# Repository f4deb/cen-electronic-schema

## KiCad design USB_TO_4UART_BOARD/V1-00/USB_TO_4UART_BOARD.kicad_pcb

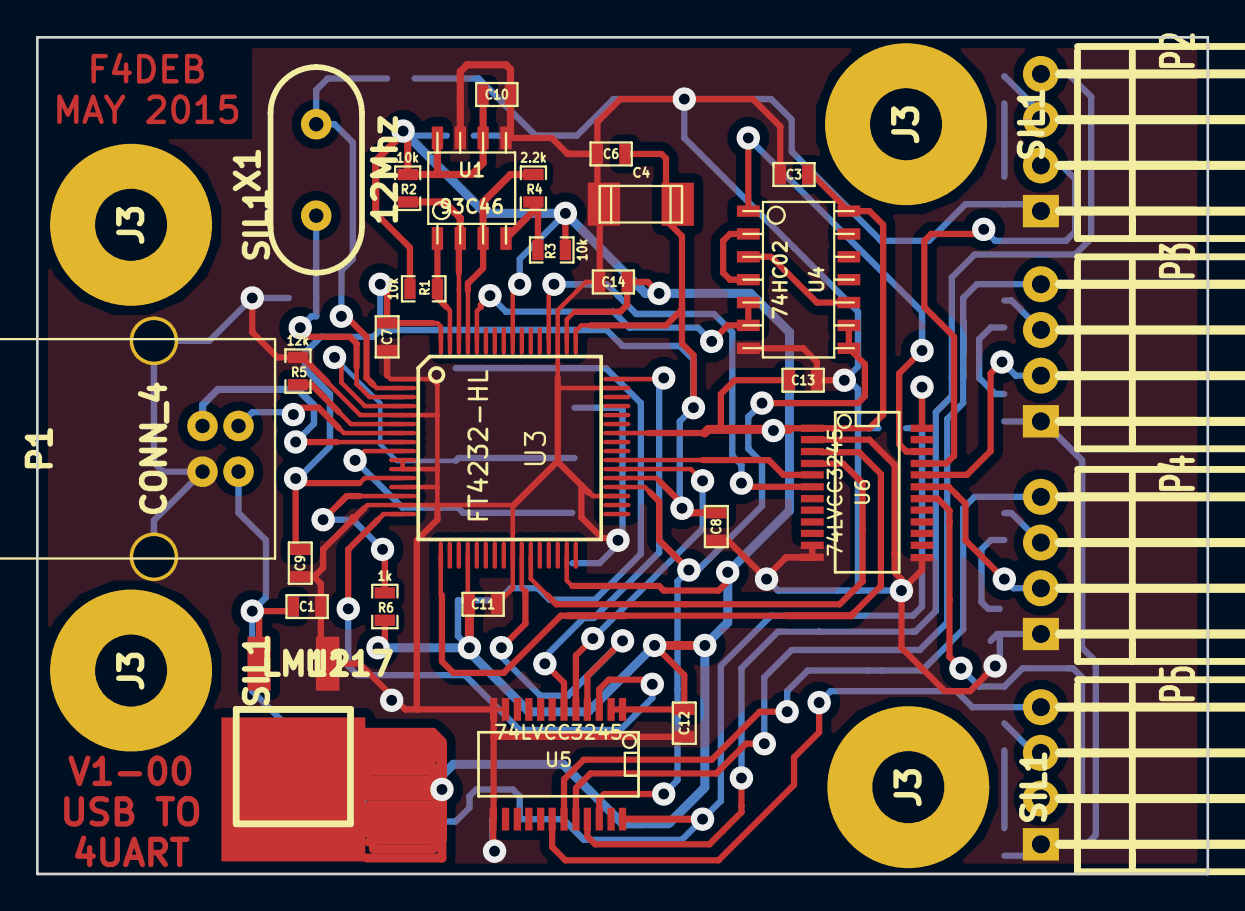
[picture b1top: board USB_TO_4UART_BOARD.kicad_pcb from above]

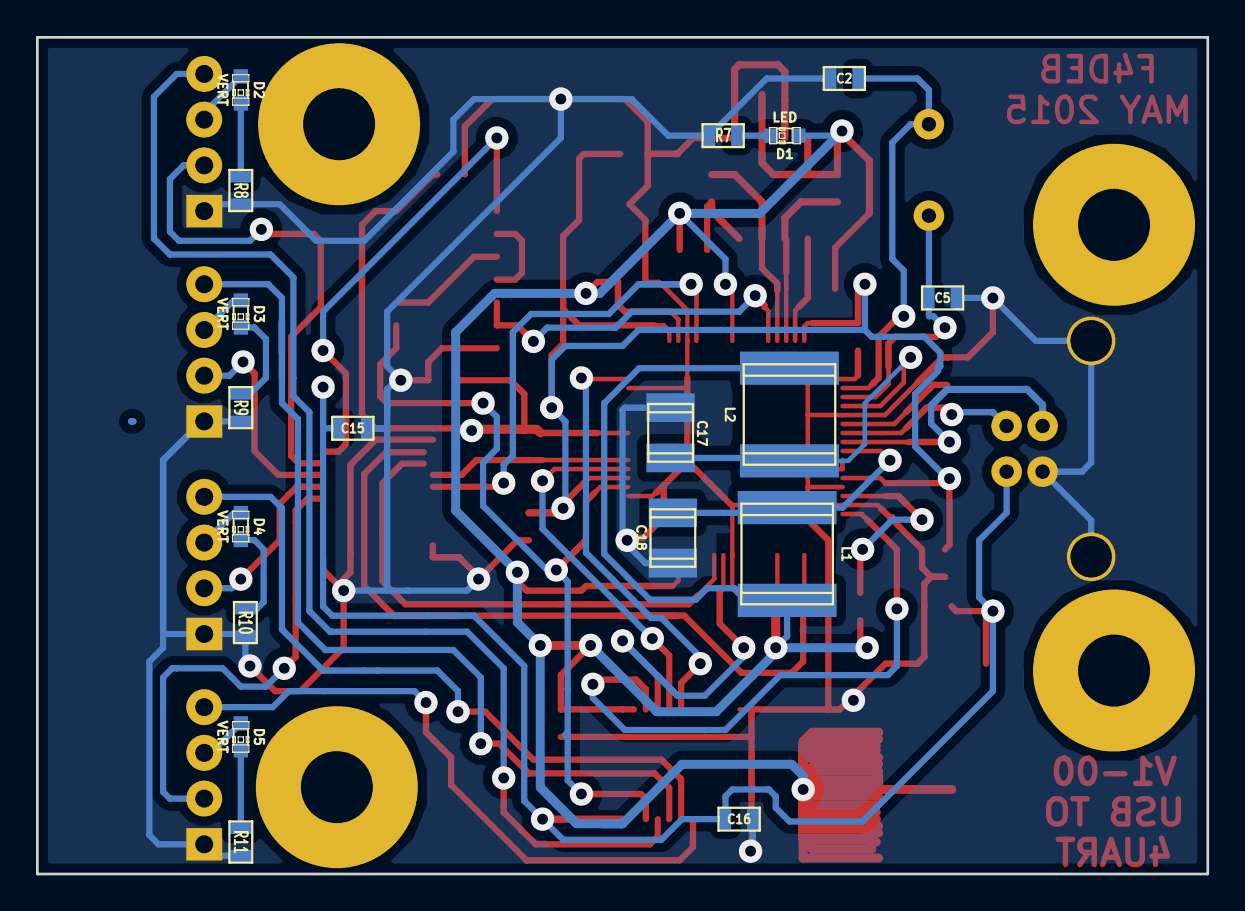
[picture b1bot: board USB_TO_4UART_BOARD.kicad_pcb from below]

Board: 2 copper layers, 65.0 x 46.5 mm, 52 parts (18 on the bottom side), 46 nets.

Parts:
C1, C3, C6, C7, C8, C9, C10, C11, C12, C13, C14, C15, C16: 100n; SM0603_Capa
C2, C5: 27p; SM0603_Capa
C4: 10uF/10V; c_1808
C17, C18: 10uF/10V; SM1210
D1: LED; LED-0603
D2, D3, D4, D5: VERT; LED-0603
J3, J3#2, J3#3, J3#4: SIL1; COLONETTE
L1, L2: 39uH; c_2220
P1: CONN_4; USB_B
P2, P3, P4, P5: CONN_4; SIL-3_1_2-4-HOR
R1, R2, R3: 10k; SM0603_Resistor
R4: 2.2k; SM0603_Resistor
R5: 12k; SM0603_Resistor
R6, R8, R9, R10, R11: 1k; SM0603_Resistor
R7: 470; SM0603_Resistor
U1: 93C46; so-8
U2: LM1117; DPAK
U3: FT4232-HL; TQFP_64
U4: 74HC02; so-14
U5, U6: 74LVCC3245; SSOP24
X1: 12Mhz; HC-49V

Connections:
+1.8V: C4.1, C6.1, C7.1, C8.1, C9.1, U3.12, U3.37, U3.49, U3.64
+3.3V: C3.1, C10.1, C11.1, C12.1, C13.1, C14.1, D1.1, L1.1, L2.1, R1.1, R2.1, R3.1, R6.2, U1.6, U1.8, U2.3, U3.20, U3.31, U3.42, U3.50, U3.56, U4.14, U5.1, U5.2, U6.1
+5VD: C1.1, C15.1, C16.1, P1.1, U2.2, U5.24, U6.24
/PWREN: U3.60, U4.5, U4.6
/RXD0: U3.17, U6.3
/RXD0_5V: P2.2, U6.21
/RXD1: U3.27, U6.4
/RXD1_5V: P3.2, U6.20
/RXD2: U3.39, U6.5
/RXD2_5V: P4.2, U6.19
/RXD3: U3.52, U6.6
/RXD3_5V: P5.2, U6.18
/SUSPEND: U3.36, U4.8, U4.9, U5.22
/TXD0: U3.16, U5.3
/TXD0_5V: P2.4, U5.21
/TXD1: U3.26, U5.4
/TXD1_5V: P3.4, U5.20
/TXD2: U3.38, U5.5
/TXD2_5V: P4.4, U5.19
/TXD3: U3.48, U5.6
/TXD3_5V: P5.4, U5.18
/UART0: D2.1, P2.3
/UART1: D3.1, P3.3
/UART2: D4.1, P4.3
/UART3: D5.1, P5.3
GND: C1.2, C2.1, C3.2, C4.2, C5.1, C6.2, C7.2, C8.2, C9.2, C10.2, C11.2, C12.2, C13.2, C14.2, C15.2, C16.2, C17.2, C18.2, P1.4, P1.5, P1.6, P2.1, P3.1, P4.1, P5.1, R5.1, R7.2, R8.2, R9.2, R10.2, R11.2, U1.5, U1.7, U2.1, U3.1, U3.5, U3.10, U3.11, U3.13, U3.15, U3.25, U3.35, U3.47, U3.51, U4.7, U5.11, U5.12, U5.13, U6.2, U6.11, U6.12, U6.13
unnamed: R5.2, U3.6
unnamed: R6.1, U3.14
unnamed: P1.2, U3.7
unnamed: P1.3, U3.8
unnamed: D4.2, R10.1
unnamed: D5.2, R11.1
unnamed: D2.2, R8.1
unnamed: D3.2, R9.1
unnamed: D1.2, R7.1
unnamed: U4.1, U6.22
unnamed: U4.2, U4.4
unnamed: U4.3, U4.10
unnamed: C18.1, L1.2, U3.9
unnamed: C17.1, L2.2, U3.4
unnamed: C2.2, U3.2, X1.2
unnamed: C5.2, U3.3, X1.1
unnamed: R3.2, R4.2, U1.4
unnamed: R2.2, U1.2, U3.62
unnamed: R1.2, U1.1, U3.63
unnamed: R4.1, U1.3, U3.61
